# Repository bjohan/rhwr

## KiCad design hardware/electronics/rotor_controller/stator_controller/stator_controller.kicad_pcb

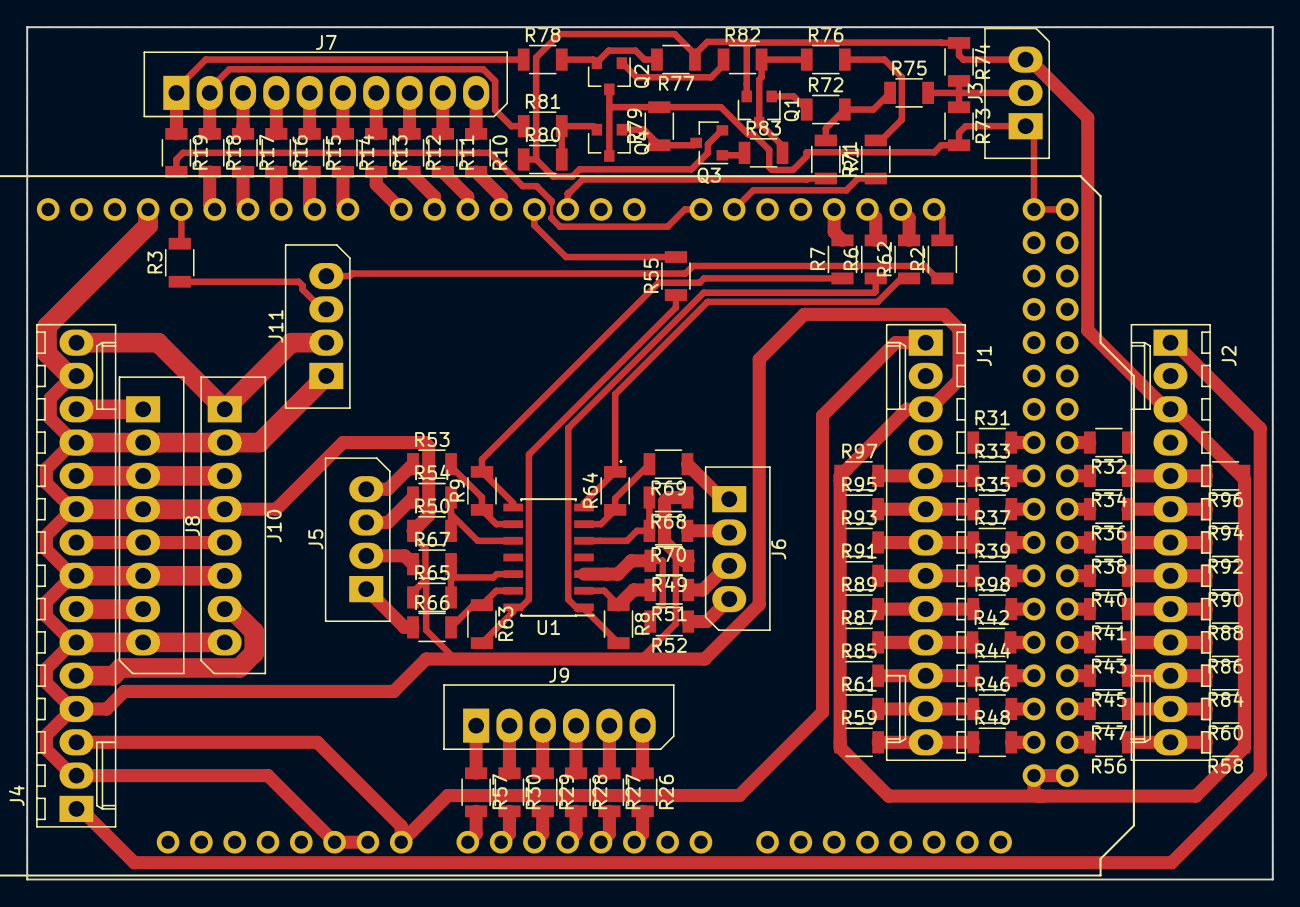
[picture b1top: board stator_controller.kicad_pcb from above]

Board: 2 copper layers, 95.0 x 65.0 mm, 107 parts (0 on the bottom side), 120 nets.

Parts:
J1, J2: Conn_01x13_Male; Molex_KK-6410-13_13x2.54mm_Straight
J3: Conn_01x03_Male; Molex_SPOX-5267_22-03-5035_03x2.54mm_Straight
J4: Conn_01x15_Male; Molex_KK-6410-15_15x2.54mm_Straight
J5, J6, J11: Conn_01x04_Male; Molex_SPOX-5267_22-03-5045_04x2.54mm_Straight
J7: Conn_01x10_Male; Molex_SPOX-5267_22-03-5105_10x2.54mm_Straight
J8, J10: Conn_01x08_Male; Molex_SPOX-5267_22-03-5085_08x2.54mm_Straight
J9: Conn_01x06_Male; Molex_SPOX-5267_22-03-5065_06x2.54mm_Straight
Q1, Q2, Q3, Q4: Q_NPN_BEC; SOT-23
R1, R2, R3, R6, R7, R8, R9, R10, R11, R12, R13, R14, R15, R16, R17, R18, R19, R26, R27, R28, R29, R30, R31, R32, R33, R34, R35, R36, R37, R38, R39, R40, R41, R42, R43, R44, R45, R46, R47, R48, R49, R50, R51, R52, R53, R54, R55, R56, R57, R58, R59, R60, R61, R62, R63, R64, R65, R66, R67, R68, R69, R70, R71, R72, R73, R74, R75, R76, R77, R78, R79, R80, R81, R82, R83, R84, R85, R86, R87, R88, R89, R90, R91, R92, R93, R94, R95, R96, R97, R98: R; R_1206
U1: LM324; SOIC-14_3.9x8.7mm_Pitch1.27mm
XA1: Arduino_Mega2560_Shield

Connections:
+5V: J3.1, Q2.3, Q4.3, R73.2, R79.2, XA1.5V3, XA1.5V4
/8V_IN_HI: J4.5, J10.7, U1.4
/8V_IN_LO: J4.7, J8.7
/11V_IN_HI: J2.1, J4.1
/18V_IN_HI: J4.15, J10.1, J11.2
/18V_IN_LO: J4.13, J8.1
/-8V_IN: J4.9, J8.5, J10.5, U1.11
/-18V_IN: J4.11, J8.3, J10.3
/AUTOCAL_ENABLE: R1.2, R76.2
/BL_HI: J9.4, R28.1
/BL_LO: J7.8, R12.1
/BT: J7.2, R18.1, R81.1
/CAL_TRIG: R71.2, XA1.D2
/CE_LO_HI: J2.6, R36.1, R94.2
/CE_LO_LO: J1.6, R35.1, R95.2
/CSB_LO_HI: J2.12, R47.1, R60.2
/CSB_LO_LO: J1.12, R46.1, R61.2
/FAN_PWM: J11.3, R3.1
/G_HI: J9.6, R26.1
/G_LO: J7.10, R10.1
/HRU: J9.2, R30.1
/HS1: J5.4, R53.1
/HS1_SE: R7.2, XA1.D18
/HS2: J5.2, R67.1
/HS2_SE: R55.2, XA1.D3
/LRU1: J7.6, R14.1
/LRU2: J7.4, R16.1
/LS1: J6.4, R52.1
/LS1_SE: R6.2, XA1.D19
/LS2: J6.2, R70.1
/LS2_SE: R62.2, XA1.D20
/MUX_LO_HI: J2.11, R45.1, R84.2
/MUX_LO_LO: J1.11, R44.1, R85.2
/RAMPCLK_LO_HI: J2.8, R40.1, R90.2
/RAMPCLK_LO_LO: J1.8, R39.1, R91.2
/RAMPDIR_LO_HI: J2.7, R38.1, R92.2
/RAMPDIR_LO_LO: J1.7, R37.1, R93.2
/SCK_LO_HI: J2.9, R41.1, R88.2
/SCK_LO_LO: J1.9, R89.2, R98.1
/SDI_LO_HI: J2.10, R43.1, R86.2
/SDI_LO_LO: J1.10, R42.1, R87.2
/SYNC_LO_HI: J2.5, R34.1, R96.2
/SYNC_LO_LO: J1.5, R33.1, R97.2
/SYSREFREQ_LO_HI: J2.13, R56.1, R58.2
/SYSREFREQ_LO_LO: J1.13, R48.1, R59.2
/TACH: J11.4, R2.1
/~BL_HI: J9.3, R29.1
/~BL_LO: J7.7, R13.1
/~BT: J7.1, R19.1, R78.1
/~G_HI: J9.5, R27.1
/~G_LO: J7.9, R11.1
/~HRU: J9.1, R57.1
/~HS1: J5.3, R54.1
/~HS2: J5.1, R66.1
/~LRU1: J7.5, R15.1
/~LRU2: J7.3, R17.1
/~LS1: J6.3, R51.1
/~LS2: J6.1, R69.1
GND: J1.3, J2.3, J3.3, J4.2, J4.4, J4.6, J4.8, J4.10, J4.12, J4.14, J8.2, J8.4, J8.6, J8.8, J10.2, J10.4, J10.6, J10.8, J11.1, Q1.2, Q3.2, R49.1, R50.1, R58.1, R59.1, R60.1, R61.1, R65.1, R68.1, R74.1, R77.1, R80.1, R84.1, R85.1, R86.1, R87.1, R88.1, R89.1, R90.1, R91.1, R92.1, R93.1, R94.1, R95.1, R96.1, R97.1, XA1.GND1, XA1.GND2, XA1.GND3, XA1.GND5, XA1.GND6
unnamed: J3.2, R73.1, R74.2, R75.2
unnamed: Q1.1, R72.1
unnamed: Q1.3, R76.1, R82.2, R83.2
unnamed: Q2.1, R82.1
unnamed: Q2.2, R77.2, R78.2
unnamed: Q3.1, R83.1
unnamed: Q3.3, Q4.1, R79.1
unnamed: Q4.2, R80.2, R81.2
unnamed: R1.1, XA1.D15
unnamed: R2.2, XA1.D21
unnamed: R3.2, XA1.D13
unnamed: R6.1, R8.2, U1.1
unnamed: R7.1, R9.2, U1.8
unnamed: R10.2, XA1.D4
unnamed: R11.2, XA1.D5
unnamed: R12.2, XA1.D6
unnamed: R13.2, XA1.D7
unnamed: R14.2, XA1.D8
unnamed: R15.2, XA1.D9
unnamed: R16.2, XA1.D10
unnamed: R17.2, XA1.D11
unnamed: R18.2, XA1.D12
unnamed: R19.2, XA1.D14
unnamed: R26.2, XA1.A5
unnamed: R27.2, XA1.A4
unnamed: R28.2, XA1.A3
unnamed: R29.2, XA1.A2
unnamed: R30.2, XA1.A1
unnamed: R31.2, XA1.D34
unnamed: R32.2, XA1.D35
unnamed: R33.2, XA1.D36
unnamed: R34.2, XA1.D37
unnamed: R35.2, XA1.D38
unnamed: R36.2, XA1.D39
unnamed: R37.2, XA1.D40
unnamed: R38.2, XA1.D41
unnamed: R39.2, XA1.D42
unnamed: R40.2, XA1.D43
unnamed: R41.2, XA1.D45
unnamed: R42.2, XA1.D46
unnamed: R43.2, XA1.D47
unnamed: R44.2, XA1.D48
unnamed: R45.2, XA1.D49
unnamed: R46.2, XA1.D50
unnamed: R47.2, XA1.D51
unnamed: R48.2, XA1.D52
unnamed: R49.2, R52.2, U1.3
unnamed: R50.2, R54.2, U1.10
unnamed: R8.1, R51.2, U1.2
unnamed: R9.1, R53.2, U1.9
unnamed: R55.1, R63.2, U1.14
unnamed: R56.2, XA1.D53
unnamed: R57.2, XA1.A0
unnamed: R62.1, R64.2, U1.7
unnamed: R63.1, R66.2, U1.13
unnamed: R64.1, R69.2, U1.6
unnamed: R65.2, R67.2, U1.12
unnamed: R68.2, R70.2, U1.5
unnamed: R71.1, R72.2, R75.1
unnamed: R98.2, XA1.D44
VDD: J1.1, J4.3, XA1.VIN

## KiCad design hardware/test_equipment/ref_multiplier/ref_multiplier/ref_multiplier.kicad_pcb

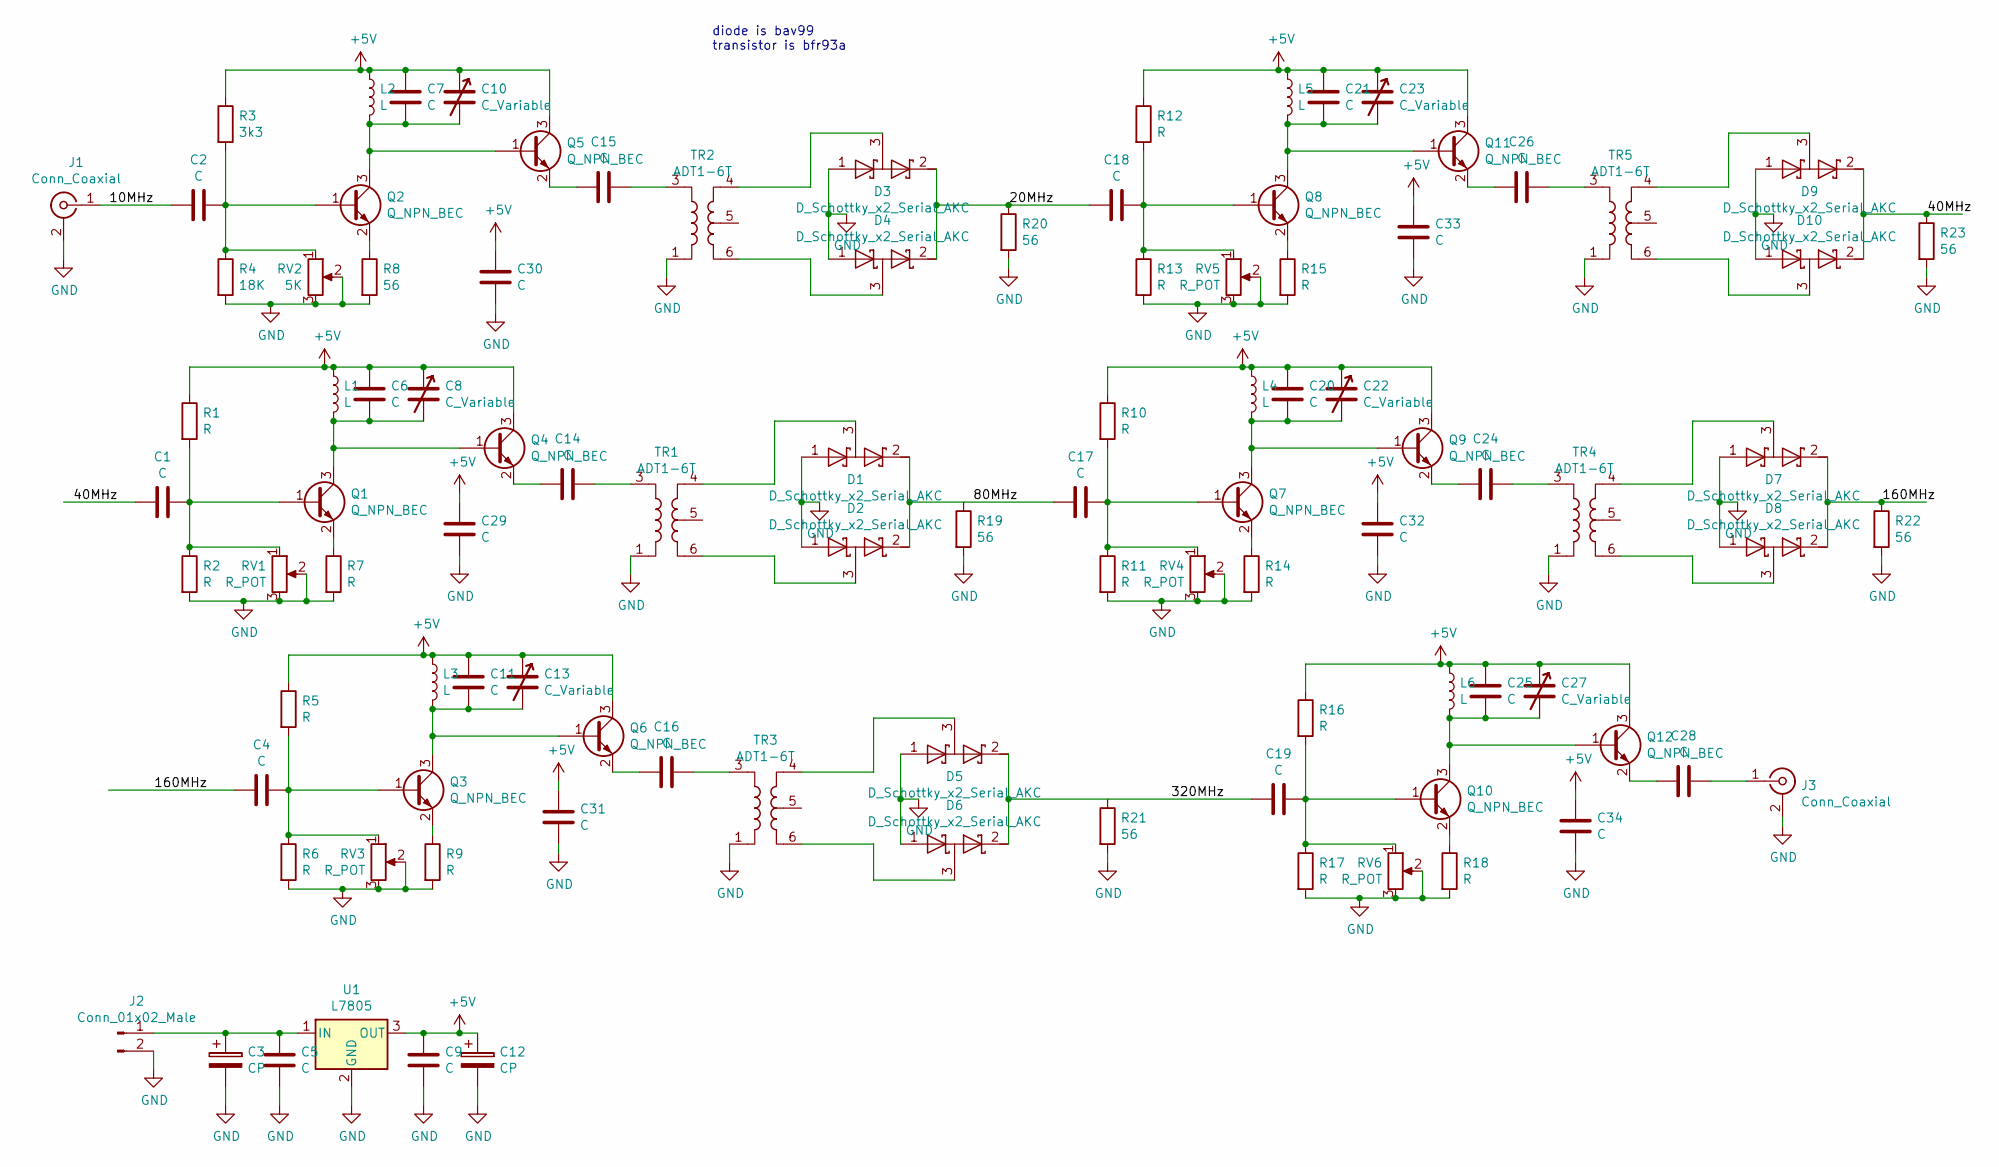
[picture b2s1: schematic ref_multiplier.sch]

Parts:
C1, C2, C4, C5, C6, C7, C9, C11, C14, C15, C16, C17, C18, C19, C20, C21, C24, C25, C26, C28, C29, C30, C31, C32, C33, C34: C; C_1206
C3, C12: CP; CP_Elec_10x10.5
C8, C10, C13, C22, C23, C27: C_Variable; C_Trimmer_Murata_TZB4-B
D1, D2, D3, D4, D5, D6, D7, D8, D9, D10: D_Schottky_x2_Serial_AKC; SOT-323_SC-70
J1, J3: Conn_Coaxial; SMA_THT_Jack_Straight
J2: Conn_01x02_Male; Molex_KK-6410-02_02x2.54mm_Straight
L1, L2, L3, L4, L5, L6: L; C_0402
Q1, Q2, Q3, Q4, Q5, Q6, Q7, Q8, Q9, Q10, Q11, Q12: Q_NPN_BEC; SOT-23
R1, R2, R5, R6, R7, R9, R10, R11, R12, R13, R14, R15, R16, R17, R18: R; R_1206
R3: 3k3; R_1206
R4: 18K; R_1206
R8, R19, R20, R21, R22, R23: 56; R_1206
RV1, RV3, RV4, RV5, RV6: R_POT; Potentiometer_Trimmer_ACP_CA9h3.8_Vertical_Px3.8mm_Py5.0mm
RV2: 5K; Potentiometer_Trimmer_ACP_CA9h3.8_Vertical_Px3.8mm_Py5.0mm
TR1, TR2, TR3, TR4, TR5: ADT1-6T; Pin_Header_Straight_2x03_Pitch1.27mm_SMD
U1: L7805; TO-220

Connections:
+5V: C6.1, C7.1, C8.1, C9.1, C10.1, C11.1, C12.1, C13.1, C20.1, C21.1, C22.1, C23.1, C25.1, C27.1, C29.1, C30.1, C31.1, C32.1, C33.1, C34.1, L1.1, L2.1, L3.1, L4.1, L5.1, L6.1, Q4.3 (C), Q5.3 (C), Q6.3 (C), Q9.3 (C), Q11.3 (C), Q12.3 (C), R1.1, R3.1, R5.1, R10.1, R12.1, R16.1, U1.3 (OUT)
/10MHz: C2.2, J1.1 (In)
/20MHz: C18.2, D3.2 (K), D4.2 (K), R20.1
/40MHz: C1.2, D9.2 (K), D10.2 (K), R23.1
/80MHz: C17.2, D1.2 (K), D2.2 (K)
/160MHz: C4.2, D7.2 (K), D8.2 (K), R22.1
/320MHz: C19.2, D5.2 (K), D6.2 (K)
GND: C3.2, C5.2, C9.2, C12.2, C29.2, C30.2, C31.2, C32.2, C33.2, C34.2, D1.1 (A), D2.1 (A), D3.1 (A), D4.1 (A), D5.1 (A), D6.1 (A), D7.1 (A), D8.1 (A), D9.1 (A), D10.1 (A), J1.2 (Ext), J2.2, J3.2 (Ext), R2.2, R4.2, R6.2, R7.2, R8.2, R9.2, R11.2, R13.2, R14.2, R15.2, R17.2, R18.2, R19.2, R20.2, R21.2, R22.2, R23.2, RV1.2, RV1.3, RV2.2, RV2.3, RV3.2, RV3.3, RV4.2, RV4.3, RV5.2, RV5.3, RV6.2, RV6.3, TR1.1, TR2.1, TR3.1, TR4.1, TR5.1, U1.2 (GND)
unnamed: C1.1, Q1.1 (B), R1.2, R2.1, RV1.1
unnamed: C2.1, Q2.1 (B), R3.2, R4.1, RV2.1
unnamed: C3.1, C5.1, J2.1, U1.1 (IN)
unnamed: C4.1, Q3.1 (B), R5.2, R6.1, RV3.1
unnamed: C6.2, C8.2, L1.2, Q1.3 (C), Q4.1 (B)
unnamed: C7.2, C10.2, L2.2, Q2.3 (C), Q5.1 (B)
unnamed: C11.2, C13.2, L3.2, Q3.3 (C), Q6.1 (B)
unnamed: C14.1, TR1.3
unnamed: C14.2, Q4.2 (E)
unnamed: C15.1, TR2.3
unnamed: C15.2, Q5.2 (E)
unnamed: C16.1, TR3.3
unnamed: C16.2, Q6.2 (E)
unnamed: C17.1, Q7.1 (B), R10.2, R11.1, RV4.1
unnamed: C18.1, Q8.1 (B), R12.2, R13.1, RV5.1
unnamed: C19.1, Q10.1 (B), R16.2, R17.1, RV6.1
unnamed: C20.2, C22.2, L4.2, Q7.3 (C), Q9.1 (B)
unnamed: C21.2, C23.2, L5.2, Q8.3 (C), Q11.1 (B)
unnamed: C24.1, TR4.3
unnamed: C24.2, Q9.2 (E)
unnamed: C25.2, C27.2, L6.2, Q10.3 (C), Q12.1 (B)
unnamed: C26.1, TR5.3
unnamed: C26.2, Q11.2 (E)
unnamed: C28.1, J3.1 (In)
unnamed: C28.2, Q12.2 (E)
unnamed: D1.3 (common), TR1.4
unnamed: D2.3 (common), TR1.6
unnamed: D3.3 (common), TR2.4
unnamed: D4.3 (common), TR2.6
unnamed: D5.3 (common), TR3.4
unnamed: D6.3 (common), TR3.6
unnamed: D7.3 (common), TR4.4
unnamed: D8.3 (common), TR4.6
unnamed: D9.3 (common), TR5.4
unnamed: D10.3 (common), TR5.6
unnamed: Q1.2 (E), R7.1
unnamed: Q2.2 (E), R8.1
unnamed: Q3.2 (E), R9.1
unnamed: Q7.2 (E), R14.1
unnamed: Q8.2 (E), R15.1
unnamed: Q10.2 (E), R18.1

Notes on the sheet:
diode is bav99 transistor is bfr93a

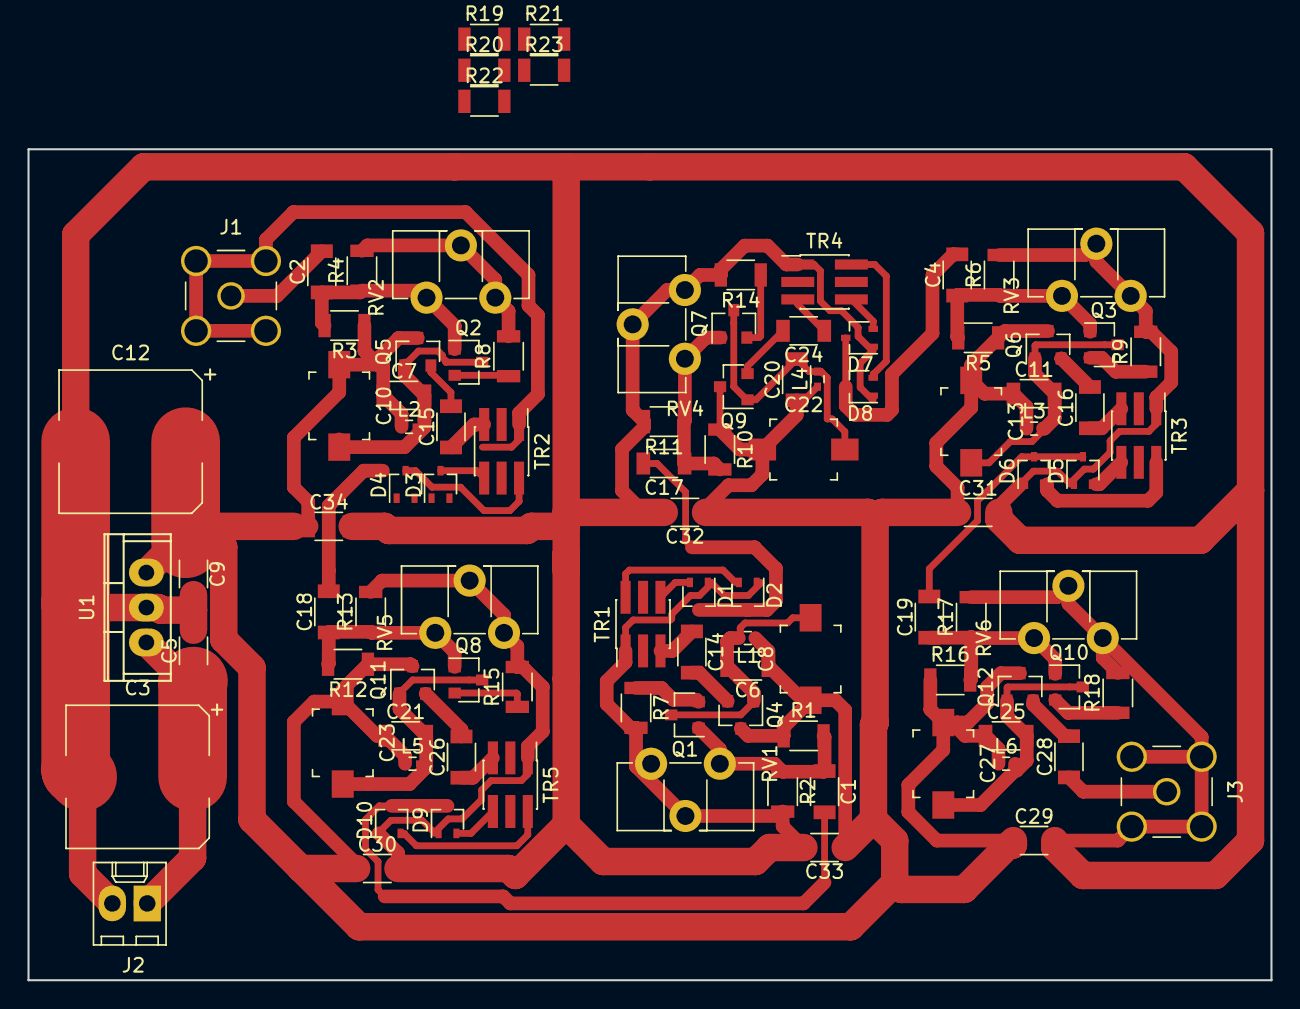
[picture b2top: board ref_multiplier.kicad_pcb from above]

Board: 2 copper layers, 90.4 x 60.5 mm, 100 parts (0 on the bottom side), 49 nets.

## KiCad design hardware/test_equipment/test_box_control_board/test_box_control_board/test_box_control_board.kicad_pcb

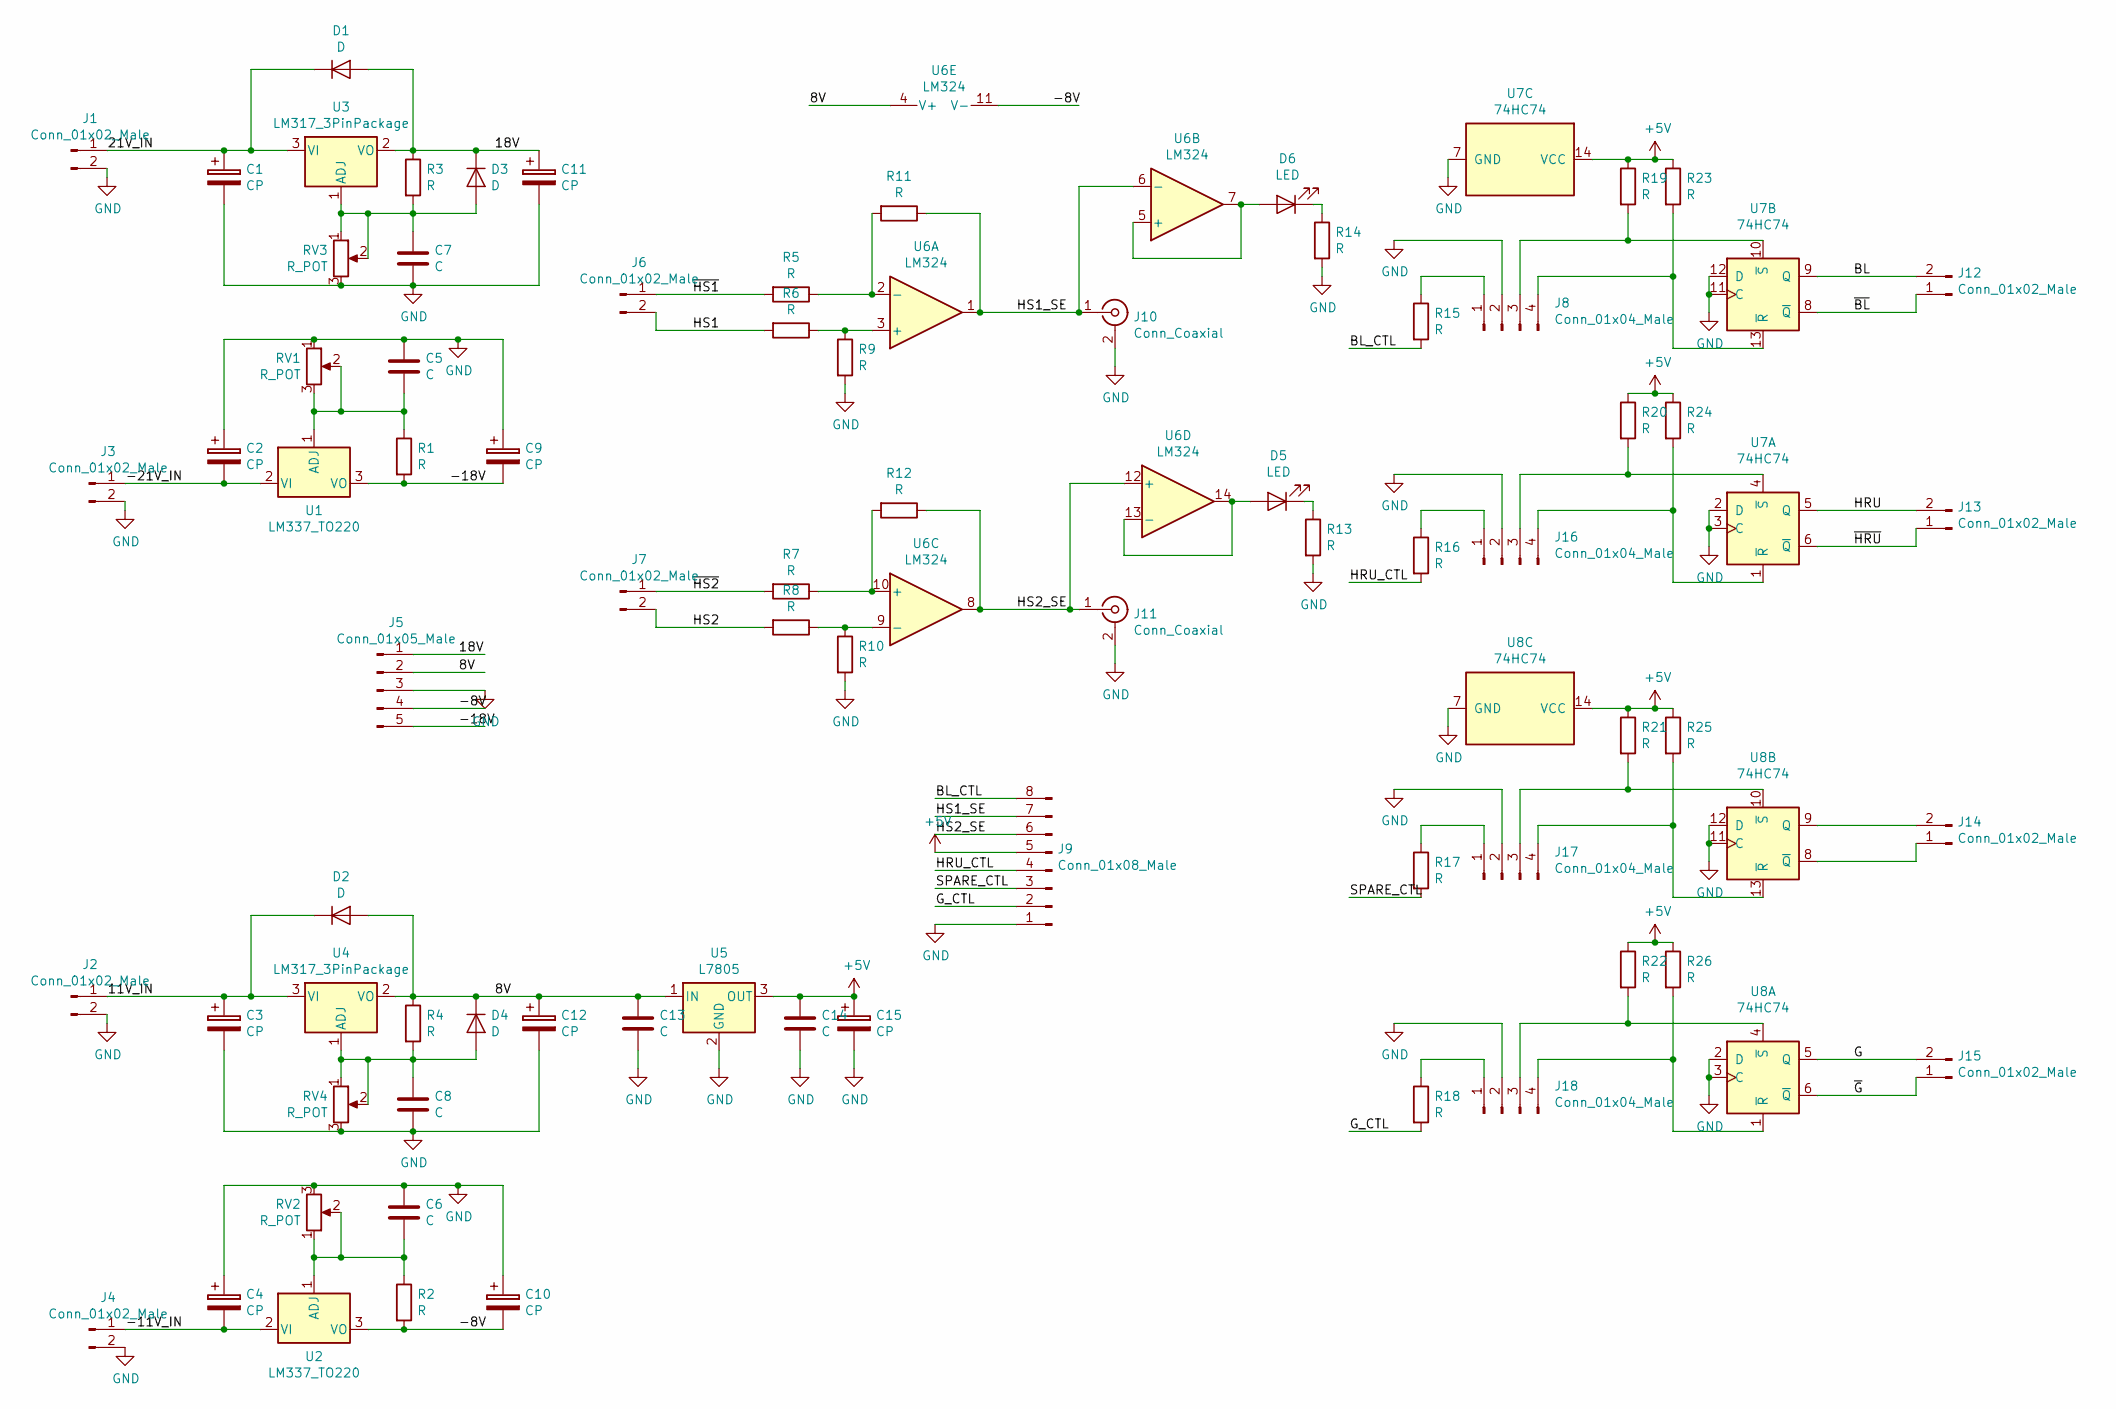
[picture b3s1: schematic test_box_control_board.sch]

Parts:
C1, C2, C3, C4, C9, C10, C11, C12, C15: CP; CP_Elec_10x10.5
C5, C6, C7, C8, C13, C14: C; C_1206
D1, D2, D3, D4: D; D_2010
D5, D6: LED; LED_1206
J1, J2, J3, J4, J6, J7, J12, J13, J14, J15: Conn_01x02_Male; Molex_KK-6410-02_02x2.54mm_Straight
J5: Conn_01x05_Male; Molex_KK-6410-05_05x2.54mm_Straight
J8, J16, J17, J18: Conn_01x04_Male; Molex_KK-6410-04_04x2.54mm_Straight
J9: Conn_01x08_Male; Molex_KK-6410-08_08x2.54mm_Straight
J10, J11: Conn_Coaxial; Molex_KK-6410-02_02x2.54mm_Straight
R1, R2, R3, R4, R5, R6, R7, R8, R9, R10, R11, R12, R13, R14, R15, R16, R17, R18, R19, R20, R21, R22, R23, R24, R25, R26: R; R_1206
RV1, RV2, RV3, RV4: R_POT; Potentiometer_Trimmer_ACP_CA6VSMD_Horizontal
U1, U2: LM337_TO220; TO-220-3_Vertical
U3, U4: LM317_3PinPackage; TO-220-3_Vertical
U5: L7805; TO-220-3_Vertical
U6: LM324; SOIC-14_3.9x8.7mm_Pitch1.27mm
U7, U8: 74HC74; SOIC-14_3.9x8.7mm_Pitch1.27mm

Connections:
+5V: C14.1, C15.1, J9.5, R19.1, R20.1, R21.1, R22.1, R23.1, R24.1, R25.1, R26.1, U5.3 (OUT), U7.14 (VCC), U8.14 (VCC)
/8V: C12.1, C13.1, D2.2 (A), D4.1 (K), J5.2, R4.1, U4.2 (VO), U5.1 (IN), U6.4 (V+)
/11V_IN: C3.1, D2.1 (K), J2.1, U4.3 (VI)
/18V: C11.1, D1.2 (A), D3.1 (K), J5.1, R3.1, U3.2 (VO)
/21V_IN: C1.1, D1.1 (K), J1.1, U3.3 (VI)
/-8V: C10.2, J5.4, R2.2, U2.3 (VO), U6.11 (V-)
/-11V_IN: C4.2, J4.1, U2.2 (VI)
/-18V: C9.2, J5.5, R1.2, U1.3 (VO)
/-21V_IN: C2.2, J3.1, U1.2 (VI)
/BL: J12.2, U7.9 (Q)
/BL_CTL: J9.8, R15.2
/G: J15.2, U8.5 (Q)
/G_CTL: J9.2, R18.2
/HRU: J13.2, U7.5 (Q)
/HRU_CTL: J9.4, R16.2
/HS1: J6.2, R6.2
/HS1_SE: J9.7, J10.1 (In), R11.1, U6.1, U6.6 (-)
/HS2: J7.2, R8.2
/HS2_SE: J9.6, J11.1 (In), R12.1, U6.8, U6.12 (+)
/SPARE_CTL: J9.3, R17.2
/~BL: J12.1, U7.8 (~Q)
/~G: J15.1, U8.6 (~Q)
/~HRU: J13.1, U7.6 (~Q)
/~HS1: J6.1, R5.2
/~HS2: J7.1, R7.2
GND: C1.2, C2.1, C3.2, C4.1, C5.1, C6.1, C7.2, C8.2, C9.1, C10.1, C11.2, C12.2, C13.2, C14.2, C15.2, J1.2, J2.2, J3.2, J4.2, J5.3, J8.2, J9.1, J10.2 (Ext), J11.2 (Ext), J16.2, J17.2, J18.2, R9.2, R10.2, R13.2, R14.2, RV1.1, RV2.3, RV3.3, RV4.3, U5.2 (GND), U7.2 (D), U7.3 (C), U7.7 (GND), U7.11 (C), U7.12 (D), U8.2 (D), U8.3 (C), U8.7 (GND), U8.11 (C), U8.12 (D)
unnamed: C5.2, R1.1, RV1.2, RV1.3, U1.1 (ADJ)
unnamed: C6.2, R2.1, RV2.1, RV2.2, U2.1 (ADJ)
unnamed: C7.1, D3.2 (A), R3.2, RV3.1, RV3.2, U3.1 (ADJ)
unnamed: C8.1, D4.2 (A), R4.2, RV4.1, RV4.2, U4.1 (ADJ)
unnamed: D5.1 (K), R13.1
unnamed: D5.2 (A), U6.13 (-), U6.14
unnamed: D6.1 (K), R14.1
unnamed: D6.2 (A), U6.5 (+), U6.7
unnamed: J8.1, R15.1
unnamed: J8.3, R19.2, U7.10 (~S)
unnamed: J8.4, R23.2, U7.13 (~R)
unnamed: J14.1, U8.8 (~Q)
unnamed: J14.2, U8.9 (Q)
unnamed: J16.1, R16.1
unnamed: J16.3, R20.2, U7.4 (~S)
unnamed: J16.4, R24.2, U7.1 (~R)
unnamed: J17.1, R17.1
unnamed: J17.3, R21.2, U8.10 (~S)
unnamed: J17.4, R25.2, U8.13 (~R)
unnamed: J18.1, R18.1
unnamed: J18.3, R22.2, U8.4 (~S)
unnamed: J18.4, R26.2, U8.1 (~R)
unnamed: R6.1, R9.1, U6.3 (+)
unnamed: R8.1, R10.1, U6.9 (-)
unnamed: R5.1, R11.2, U6.2 (-)
unnamed: R7.1, R12.2, U6.10 (+)

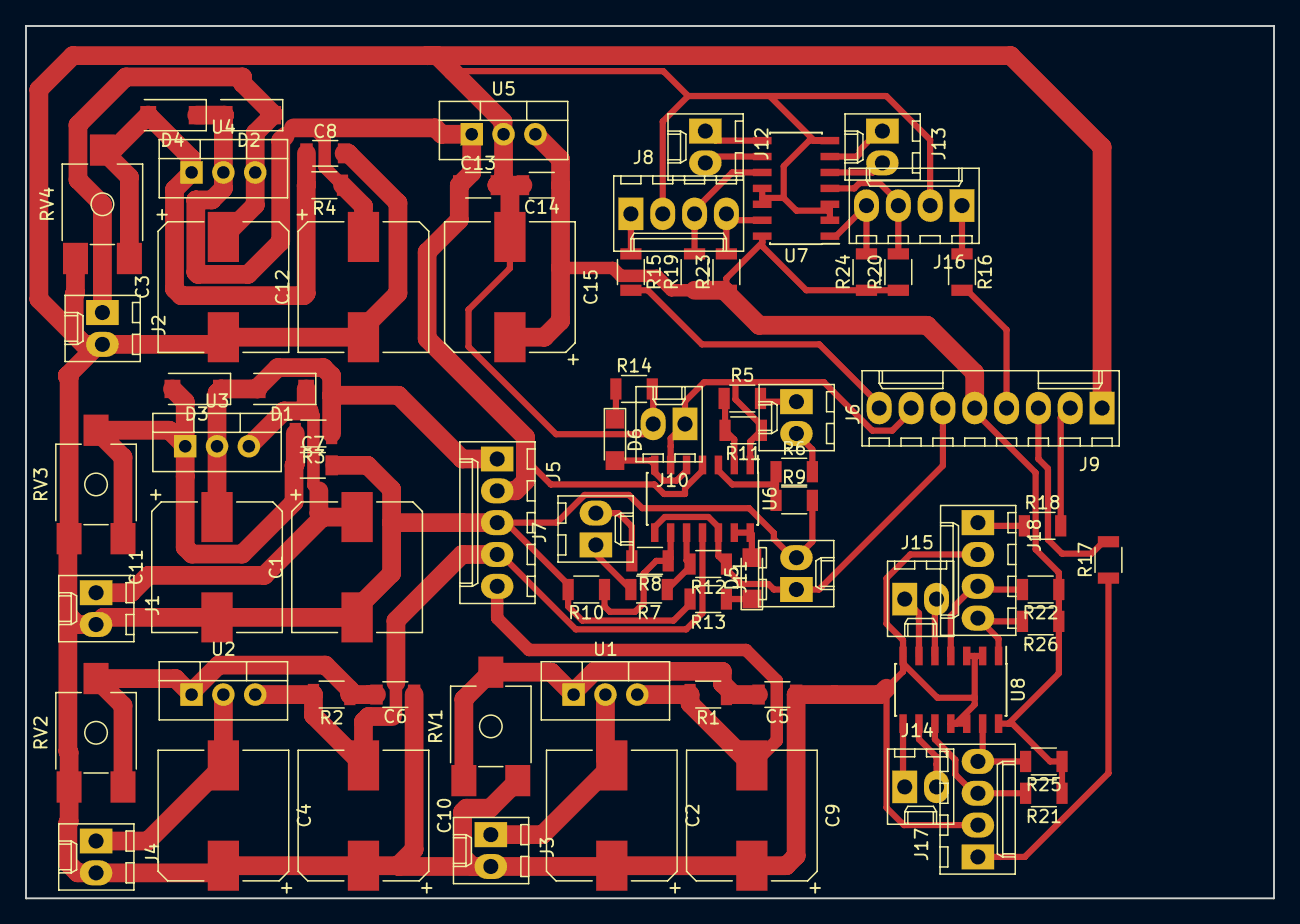
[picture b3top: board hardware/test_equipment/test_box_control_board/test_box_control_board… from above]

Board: 2 copper layers, 99.6 x 69.6 mm, 77 parts (0 on the bottom side), 52 nets.

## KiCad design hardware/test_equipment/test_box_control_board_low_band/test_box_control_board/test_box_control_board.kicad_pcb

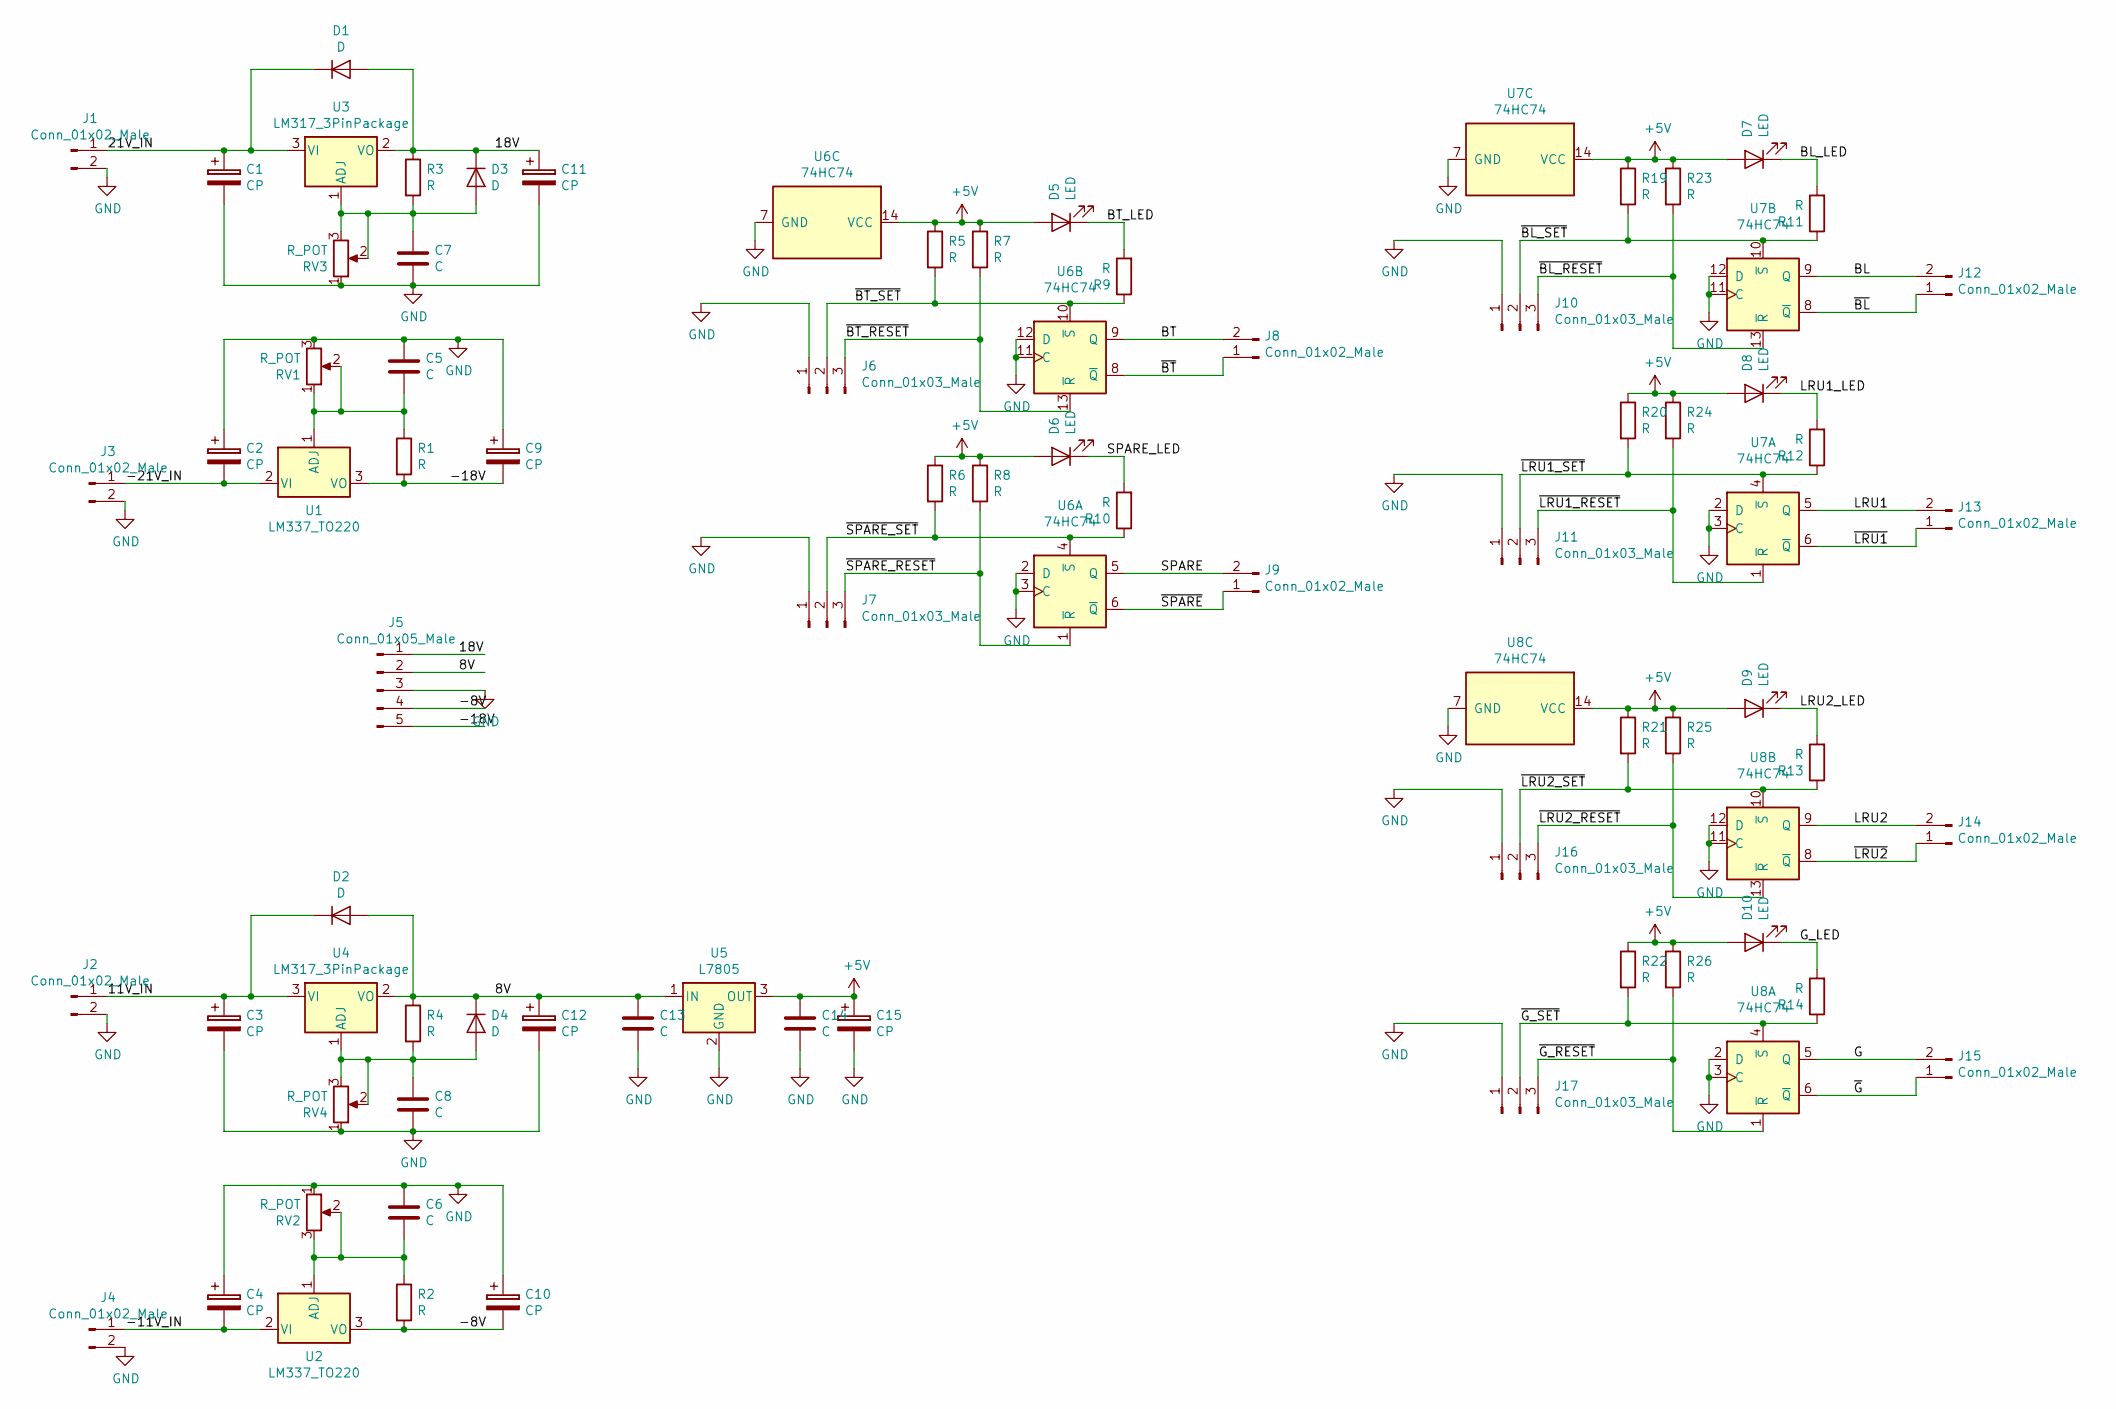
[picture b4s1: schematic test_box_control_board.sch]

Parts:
C1, C2, C3, C4, C9, C10, C11, C12, C15: CP; CP_Elec_10x10.5
C5, C6, C7, C8, C13, C14: C; C_1206
D1, D2, D3, D4: D; D_2010
D5, D6, D7, D8, D9, D10: LED; LED_1206
J1, J2, J3, J4, J8, J9, J12, J13, J14, J15: Conn_01x02_Male; Molex_KK-6410-02_02x2.54mm_Straight
J5: Conn_01x05_Male; Molex_KK-6410-05_05x2.54mm_Straight
J6, J7, J10, J11, J16, J17: Conn_01x03_Male; Molex_KK-6410-03_03x2.54mm_Straight
R1, R2, R3, R4, R5, R6, R7, R8, R9, R10, R11, R12, R13, R14, R19, R20, R21, R22, R23, R24, R25, R26: R; R_1206
RV1, RV2, RV3, RV4: R_POT; Potentiometer_Trimmer_Vishay_TS53YL
U1, U2: LM337_TO220; TO-220-3_Vertical
U3, U4: LM317_3PinPackage; TO-220-3_Vertical
U5: L7805; TO-220-3_Vertical
U6, U7, U8: 74HC74; SOIC-14_3.9x8.7mm_Pitch1.27mm

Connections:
+5V: C14.1, C15.1, D5.2 (A), D6.2 (A), D7.2 (A), D8.2 (A), D9.2 (A), D10.2 (A), R5.1, R6.1, R7.1, R8.1, R19.1, R20.1, R21.1, R22.1, R23.1, R24.1, R25.1, R26.1, U5.3 (OUT), U6.14 (VCC), U7.14 (VCC), U8.14 (VCC)
/8V: C12.1, C13.1, D2.2 (A), D4.1 (K), J5.2, R4.1, U4.2 (VO), U5.1 (IN)
/11V_IN: C3.1, D2.1 (K), J2.1, U4.3 (VI)
/18V: C11.1, D1.2 (A), D3.1 (K), J5.1, R3.1, U3.2 (VO)
/21V_IN: C1.1, D1.1 (K), J1.1, U3.3 (VI)
/-8V: C10.2, J5.4, R2.2, U2.3 (VO)
/-11V_IN: C4.2, J4.1, U2.2 (VI)
/-18V: C9.2, J5.5, R1.2, U1.3 (VO)
/-21V_IN: C2.2, J3.1, U1.2 (VI)
/BL: J12.2, U7.9 (Q)
/BL_LED: D7.1 (K), R11.2
/BT: J8.2, U6.9 (Q)
/BT_LED: D5.1 (K), R9.2
/G: J15.2, U8.5 (Q)
/G_LED: D10.1 (K), R14.2
/LRU1: J13.2, U7.5 (Q)
/LRU1_LED: D8.1 (K), R12.2
/LRU2: J14.2, U8.9 (Q)
/LRU2_LED: D9.1 (K), R13.2
/SPARE: J9.2, U6.5 (Q)
/SPARE_LED: D6.1 (K), R10.2
/~BL: J12.1, U7.8 (~Q)
/~BL_RESET: J10.3, R23.2, U7.13 (~R)
/~BL_SET: J10.2, R11.1, R19.2, U7.10 (~S)
/~BT: J8.1, U6.8 (~Q)
/~BT_RESET: J6.3, R7.2, U6.13 (~R)
/~BT_SET: J6.2, R5.2, R9.1, U6.10 (~S)
/~G: J15.1, U8.6 (~Q)
/~G_RESET: J17.3, R26.2, U8.1 (~R)
/~G_SET: J17.2, R14.1, R22.2, U8.4 (~S)
/~LRU1: J13.1, U7.6 (~Q)
/~LRU1_RESET: J11.3, R24.2, U7.1 (~R)
/~LRU1_SET: J11.2, R12.1, R20.2, U7.4 (~S)
/~LRU2: J14.1, U8.8 (~Q)
/~LRU2_RESET: J16.3, R25.2, U8.13 (~R)
/~LRU2_SET: J16.2, R13.1, R21.2, U8.10 (~S)
/~SPARE: J9.1, U6.6 (~Q)
/~SPARE_RESET: J7.3, R8.2, U6.1 (~R)
/~SPARE_SET: J7.2, R6.2, R10.1, U6.4 (~S)
GND: C1.2, C2.1, C3.2, C4.1, C5.1, C6.1, C7.2, C8.2, C9.1, C10.1, C11.2, C12.2, C13.2, C14.2, C15.2, J1.2, J2.2, J3.2, J4.2, J5.3, J6.1, J7.1, J10.1, J11.1, J16.1, J17.1, RV1.3, RV2.1, RV3.1, RV4.1, U5.2 (GND), U6.2 (D), U6.3 (C), U6.7 (GND), U6.11 (C), U6.12 (D), U7.2 (D), U7.3 (C), U7.7 (GND), U7.11 (C), U7.12 (D), U8.2 (D), U8.3 (C), U8.7 (GND), U8.11 (C), U8.12 (D)
unnamed: C5.2, R1.1, RV1.1, RV1.2, U1.1 (ADJ)
unnamed: C6.2, R2.1, RV2.2, RV2.3, U2.1 (ADJ)
unnamed: C7.1, D3.2 (A), R3.2, RV3.2, RV3.3, U3.1 (ADJ)
unnamed: C8.1, D4.2 (A), R4.2, RV4.2, RV4.3, U4.1 (ADJ)

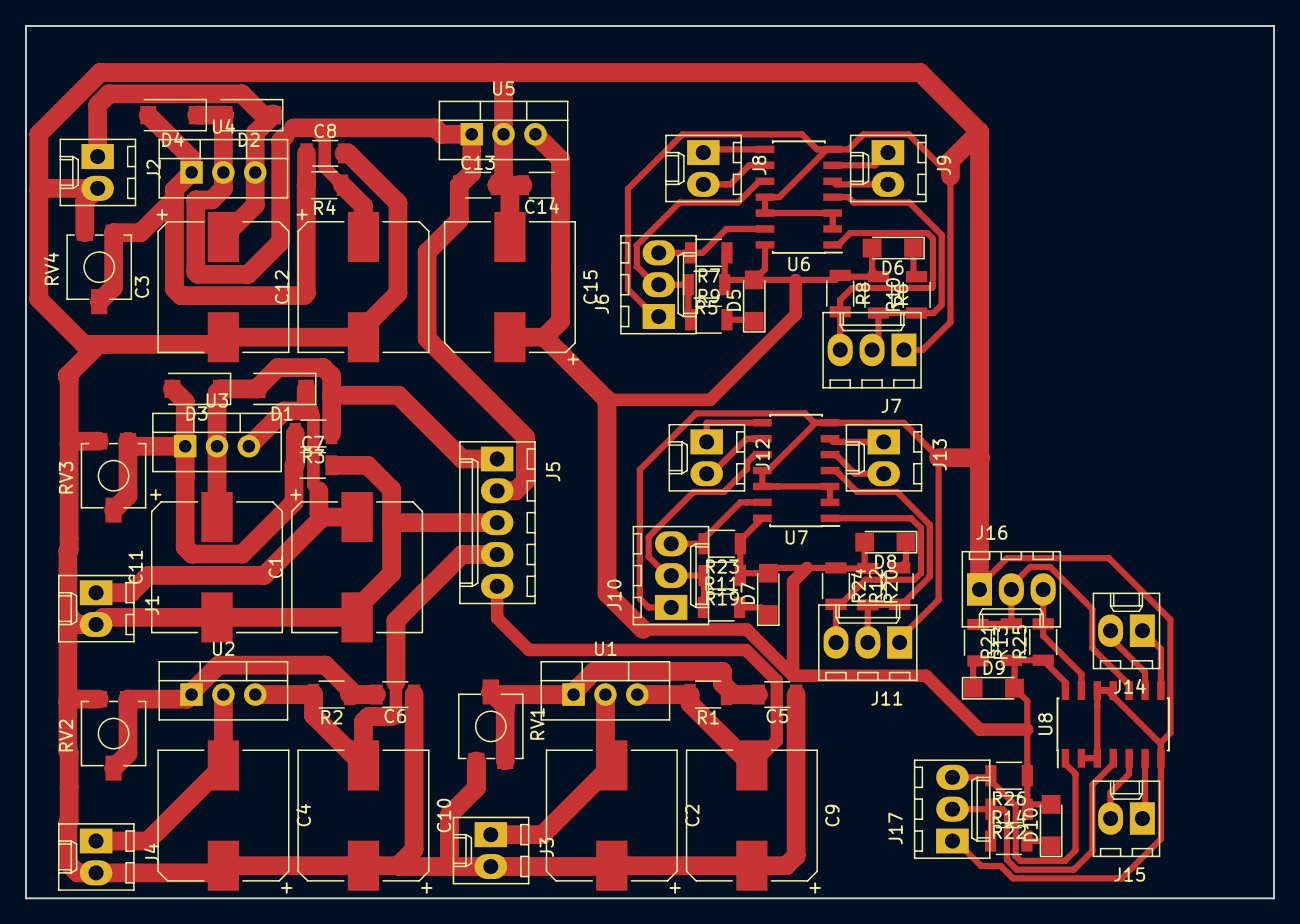
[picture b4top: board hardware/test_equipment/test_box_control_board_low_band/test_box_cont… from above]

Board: 2 copper layers, 99.6 x 69.6 mm, 76 parts (0 on the bottom side), 44 nets.
